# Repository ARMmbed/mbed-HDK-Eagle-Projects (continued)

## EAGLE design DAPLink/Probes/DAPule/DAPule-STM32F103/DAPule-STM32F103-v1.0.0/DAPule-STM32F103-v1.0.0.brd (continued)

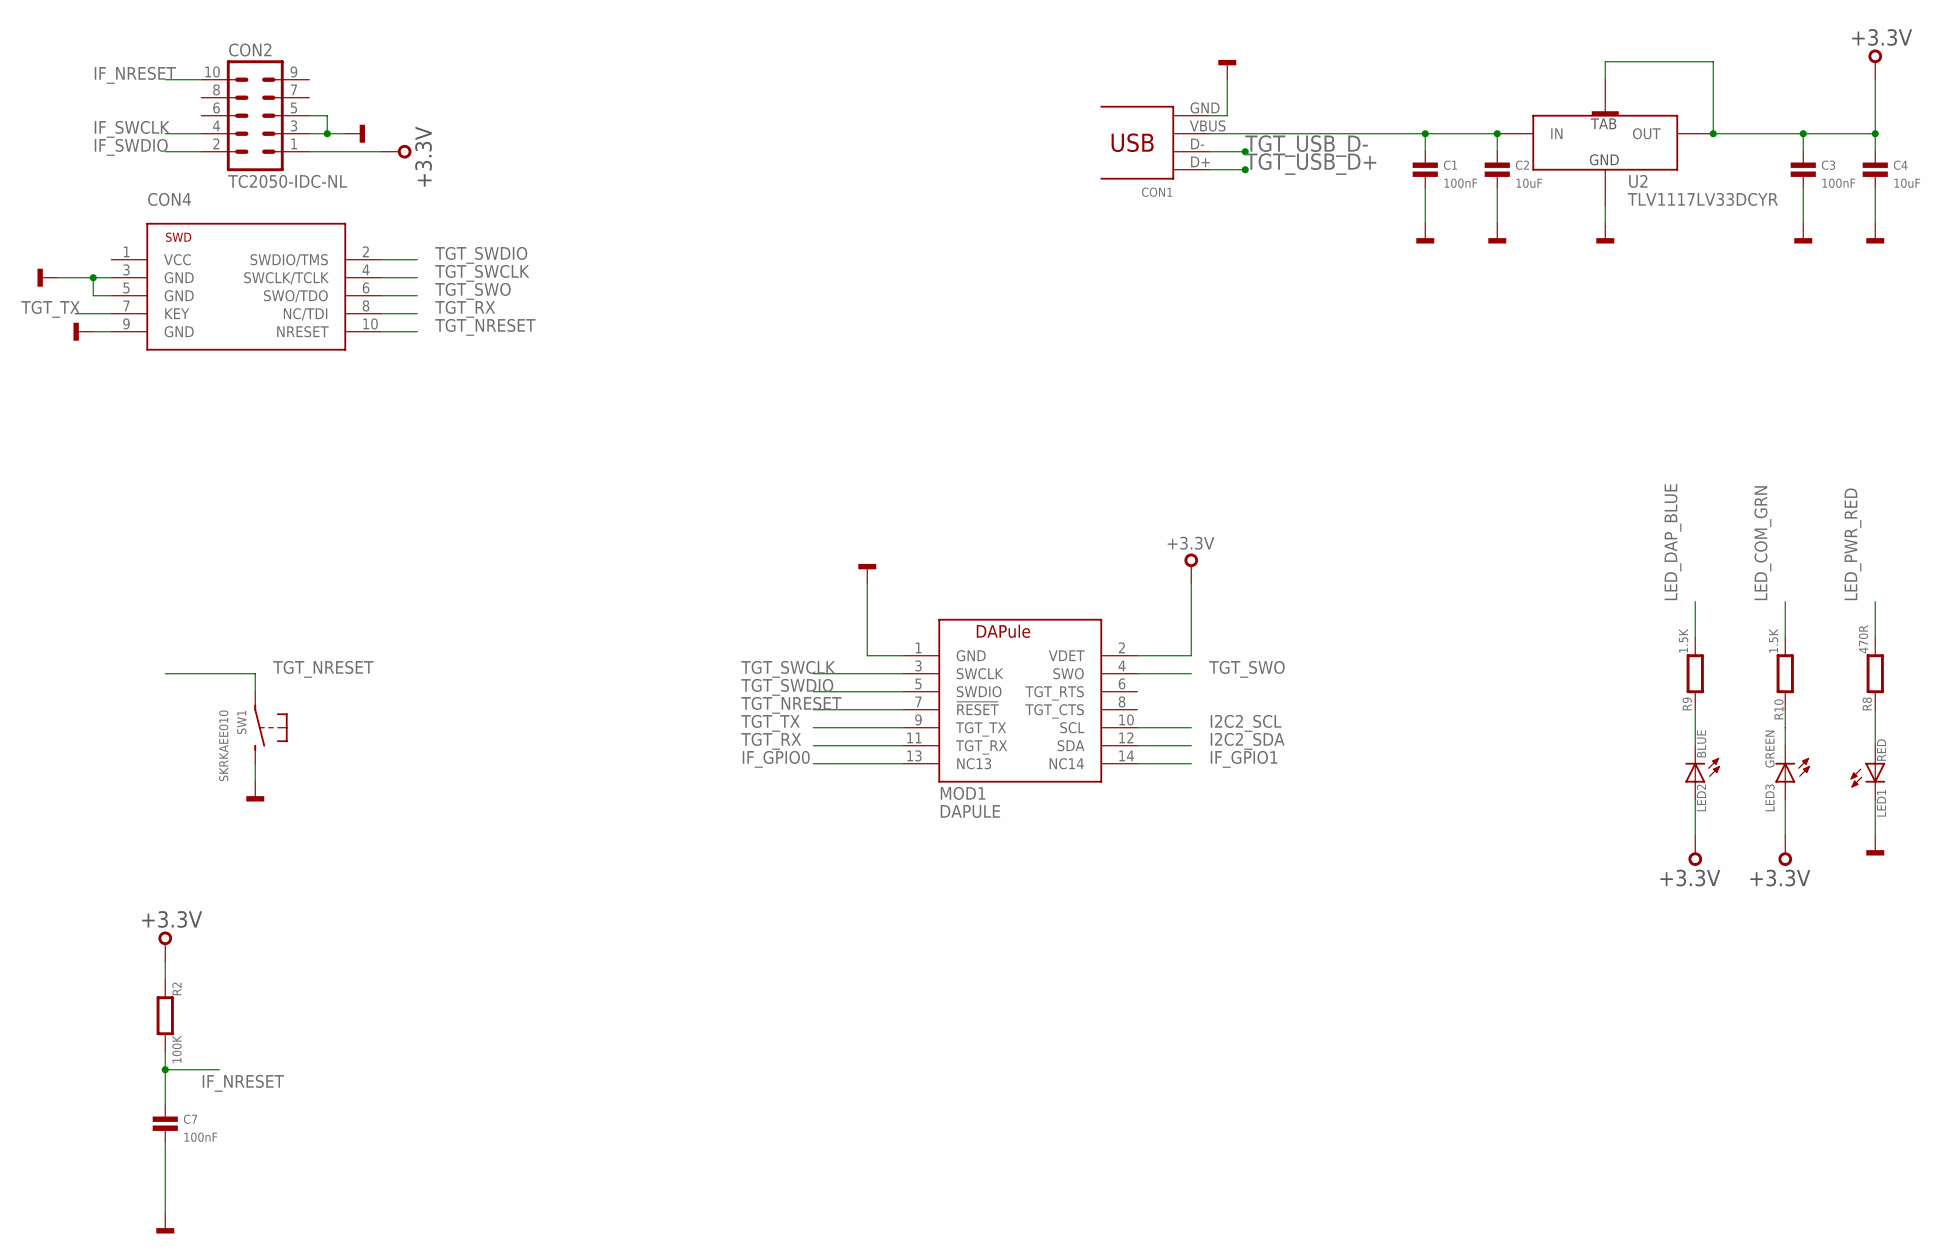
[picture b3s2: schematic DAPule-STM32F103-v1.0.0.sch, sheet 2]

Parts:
C1, C3, C7: 100nF; 0603
C2, C4: 10uF; 0603
CON1: 47346-0001; USB-MICRO-B-H
CON2: TC2050-IDC-NL
CON4: SWD-10-SMD
LED1: RED; CHIPLED_0603
LED2: BLUE; CHIPLED_0603
LED3: GREEN; CHIPLED_0603
MOD1: DAPULE
R2: 100K; 0603
R8: 470R; 0603
R9, R10: 1.5K; 0603
SW1: SKRKAEE010
U2: TLV1117LV33DCYR; SOT223

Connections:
+3.3V: C3.1, C4.1, CON2.1, LED2.A, LED3.A, MOD1.2 (VDET), R2.1, U2.OUT(1) (OUT), U2.OUT(2) (TAB); also elsewhere on the board
GND: C1.2, C2.2, C3.2, C4.2, C7.2, CON1.GND, CON2.3, CON2.5, CON4.3 (GND), CON4.5 (GND), CON4.9 (GND), LED1.C, MOD1.1 (GND), SW1.P$2 (S), U2.GND; also elsewhere on the board
I2C2_SCL: MOD1.10 (SCL); also elsewhere on the board
I2C2_SDA: MOD1.12 (SDA); also elsewhere on the board
IF_GPIO0: MOD1.13 (NC13); also elsewhere on the board
IF_GPIO1: MOD1.14 (NC14); also elsewhere on the board
IF_NRESET: C7.1, CON2.10, R2.2; also elsewhere on the board
IF_SWCLK: CON2.4; also elsewhere on the board
IF_SWDIO: CON2.2; also elsewhere on the board
LED_COM_GRN: R10.2; also elsewhere on the board
LED_DAP_BLUE: R9.2; also elsewhere on the board
LED_PWR_RED: R8.2; also elsewhere on the board
unnamed: C1.1, C2.1, CON1.VBUS, U2.IN
unnamed: LED1.A, R8.1
unnamed: LED2.C, R9.1
unnamed: LED3.C, R10.1
TGT_NRESET: CON4.10 (NRESET), MOD1.7 (!RESET), SW1.P$1; also elsewhere on the board
TGT_RX: CON4.8 (NC/TDI), MOD1.11 (TGT_RX); also elsewhere on the board
TGT_SWCLK: CON4.4 (SWCLK/TCLK), MOD1.3 (SWCLK); also elsewhere on the board
TGT_SWDIO: CON4.2 (SWDIO/TMS), MOD1.5 (SWDIO); also elsewhere on the board
TGT_SWO: CON4.6 (SWO/TDO), MOD1.4 (SWO); also elsewhere on the board
TGT_TX: CON4.7 (KEY), MOD1.9 (TGT_TX); also elsewhere on the board
TGT_USB_D+: CON1.D+; also elsewhere on the board
TGT_USB_D-: CON1.D-; also elsewhere on the board

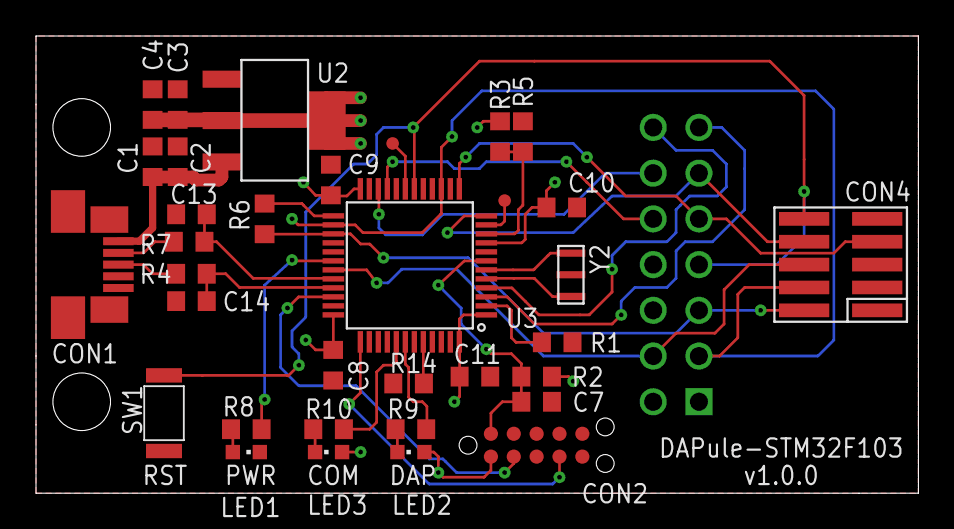
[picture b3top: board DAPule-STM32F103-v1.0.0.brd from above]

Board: 2 copper layers, 49.0 x 25.4 mm, 35 parts (0 on the bottom side), 34 nets.

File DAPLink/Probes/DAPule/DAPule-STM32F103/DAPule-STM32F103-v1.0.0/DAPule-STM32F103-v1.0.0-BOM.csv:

"Qty";"Value";"Device";"Package";"Parts";"Description";"MF";"MFN";"OC-DIGIKEY";"OC-MOUSER";"OC-NEWARK";"TP_SIGNAL_NAME";
"2";"1.5K";"RESISTOR0603";"0603";"R9, R10";"Resistor";"";"";"";"";"";"";
"2";"100K";"RESISTOR0603";"0603";"R2, R14";"Resistor";"";"";"";"";"";"";
"1";"100R";"RESISTOR0603";"0603";"R6";"Resistor";"";"";"";"";"";"";
"7";"100nF";"CAPACITOR0603";"0603";"C1, C3, C7, C8, C9, C10, C11";"Capacitor";"";"";"";"";"";"";
"1";"10K";"RESISTOR0603";"0603";"R1";"Resistor";"";"";"";"";"";"";
"2";"10uF";"CAPACITOR0603";"0603";"C2, C4";"Capacitor";"";"";"";"";"";"";
"2";"18pF";"CAPACITOR0603";"0603";"C13, C14";"Capacitor";"";"";"";"";"";"";
"2";"33R";"RESISTOR0603";"0603";"R4, R7";"Resistor";"";"";"";"";"";"";
"2";"4.7K";"RESISTOR0603";"0603";"R3, R5";"Resistor";"";"";"";"";"";"";
"1";"470R";"RESISTOR0603";"0603";"R8";"Resistor";"";"";"";"";"";"";
"1";"47346-0001";"47346-0001";"USB-MICRO-B-H";"CON1";"USB Receptacle Horizontal Micro Type B";"MOLEX";"47346-0001";"";"538-47346-0001";"1568026";"";
"1";"BLUE";"SMD_LED0603";"CHIPLED_0603";"LED2";"LED SMD, Colour Red";"Wurth Electronics Inc";"150060RS75000";"732-4978-1-ND";"710-150060RS75000";"2322071";"";
"1";"CSTCE8M00G55-R0";"CSTCE8M00G55-R0";"CSTCE8M00G55-R0";"Y2";"Resonator Cermanic, Murata 8MHz 33pF";"Murata";"CSTCE8M00G55-R0";"490-1195-1-ND";"81-CSTCE8M00G55-R0";"2443270";"";
"1";"DAPULE";"DAPULE";"DAPULE";"MOD1";"";"";"";"";"";"";"";
"1";"GREEN";"SMD_LED0603";"CHIPLED_0603";"LED3";"LED SMD, Colour Red";"Wurth Electronics Inc";"150060RS75000";"732-4978-1-ND";"710-150060RS75000";"2322071";"";
"2";"PTR1TP07R";"PTR1TP07R";"TP07R";"TP1, TP2";"TEST PIN";"";"";"";"";"";"";
"1";"RED";"SMD_LED0603";"CHIPLED_0603";"LED1";"LED SMD, Colour Red";"Wurth Electronics Inc";"150060RS75000";"732-4978-1-ND";"710-150060RS75000";"2322071";"";
"1";"SKRKAEE010";"SKRKAEE010";"SKRKAEE010";"SW1";"MOMENTARY SWITCH PUSH VERTICAL (SPST)";"ALPS";"SKRKAEE010";"";"688-SKRKAE";"";"";
"1";"STM32F103CBT6";"STM32F103CBT6";"LQFP48";"U3";"ARM® Cortex®-M3 STM32 F1 Microcontroller IC 32-Bit 72MHz 128KB (128K x 8) FLASH";"STMicroelectronics";"STM32F103CBT6";"497-6288-ND";"511-STM32F103CBT6";"11N8296";"";
"1";"SWD-10-SMD";"SWD-10-SMD";"SWD-10-SMD";"CON4";"2.54mm pitch 10-Pin Cortex Programming Header";"";"";"";"";"";"";
"1";"TC2050-IDC-NL";"TC2050-IDC-NL";"TC2050-IDC-NL";"CON2";"Tag-Connect In Circuit Programming & Debug Cable 10 Pin";"";"";"";"";"";"";
"1";"TLV1117LV33DCYR";"TLV1117LV33DCYR";"SOT223";"U2";"LDO Fixed Regulator 3.3v, 1A";"Texas Instruments";"TLV1117LV33DCYR";"296-28778-1-ND";"595-TLV1117LV33DCYR";"2323647";"";

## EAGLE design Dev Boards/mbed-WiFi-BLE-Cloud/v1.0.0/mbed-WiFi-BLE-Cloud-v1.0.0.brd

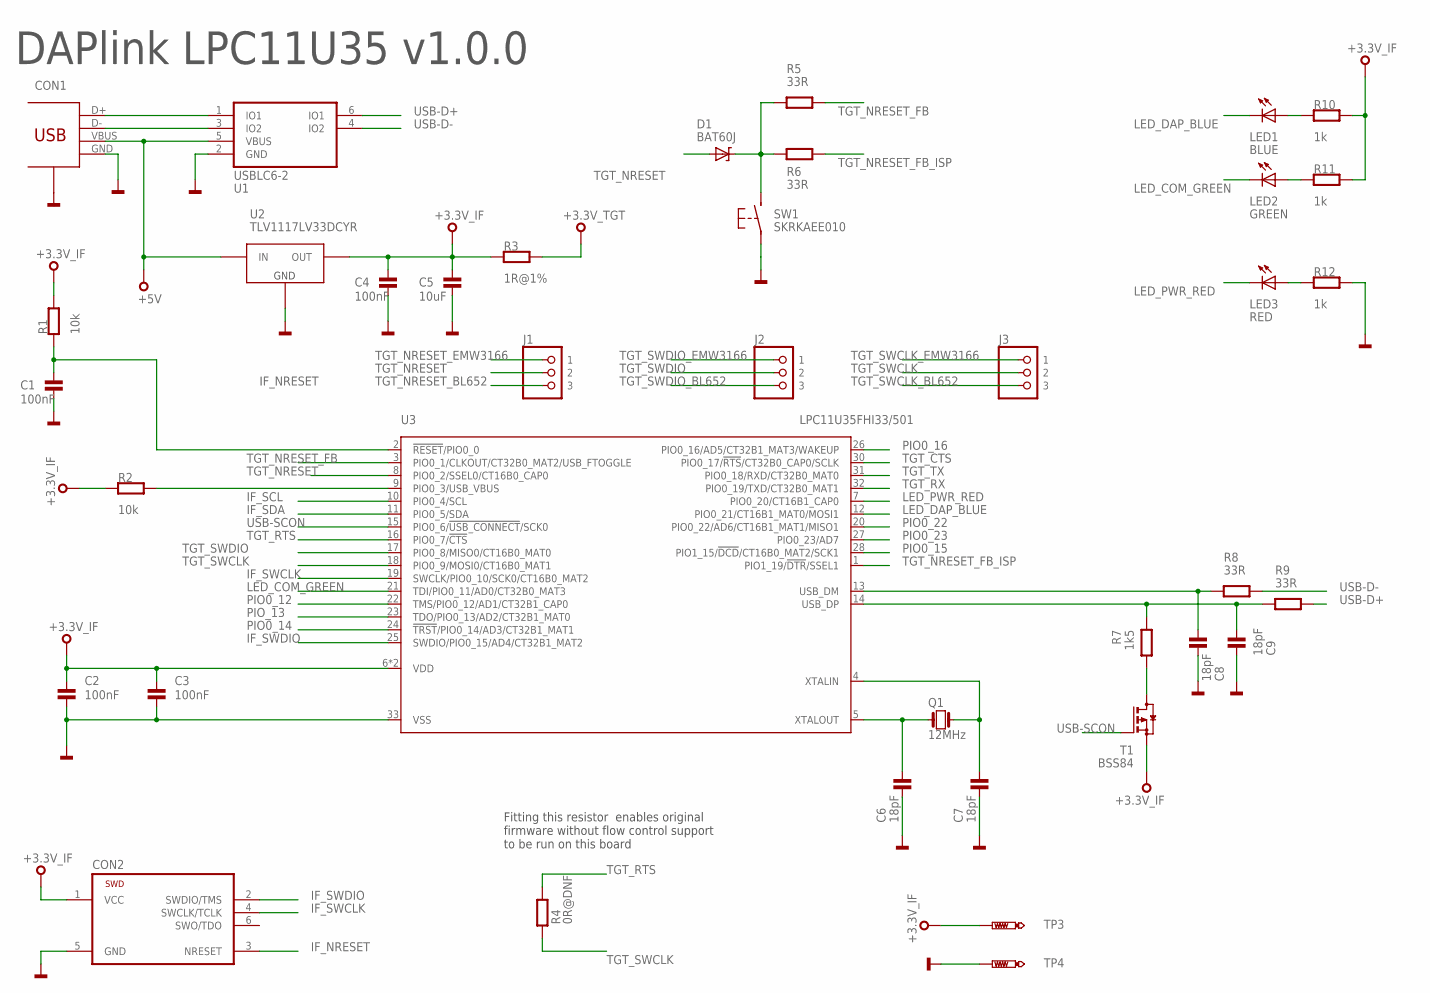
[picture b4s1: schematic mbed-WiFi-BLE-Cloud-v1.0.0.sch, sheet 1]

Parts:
C1, C2, C3, C4: 100nF; 0603
C5: 10uF; 0603
C6, C7, C8, C9: 18pF; 0603
CON1: 47346-0001; USB-MICRO-B-H
CON2: TC2030-CTX-NL
D1: BAT60J; SOD323
J1, J2, J3: PINHD-1X3; 1X03
LED1: BLUE; CHIPLED_0603
LED2: GREEN; CHIPLED_0603
LED3: RED; CHIPLED_0603
Q1: 12MHz; 3.2X.2.5
R1, R2: 10k; 0603
R3: 1R@1%; 0603
R4: 0R@DNF; 0603
R5, R6, R8, R9: 33R; 0603
R7: 1k5; 0603
R10, R11, R12: 1k; 0603
SW1: SKRKAEE010
T1: BSS84; SOT23-3
TP3, TP4: PTR1PAD1-13; P1-13
U1: USBLC6-2SC6; SOT23-6L
U2: TLV1117LV33DCYR; SOT223
U3: LPC11U35FHI33/501; SOT617-3

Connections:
+3.3V_IF: C2.1, C3.1, C4.1, C5.1, CON2.1 (VCC), R1.2, R2.1, R3.1, R10.2, R11.2, T1.2 (S), TP3.TP, U2.2 (OUT), U2.4 (OUT), U3.6 (VDD), U3.29 (VDD); also elsewhere on the board
+3.3V_TGT: R3.2; also elsewhere on the board
+5V: CON1.VBUS, U1.5 (VBUS), U2.3 (IN); also elsewhere on the board
GND: C1.2, C2.2, C3.2, C4.2, C5.2, C6.2, C7.2, C8.2, C9.2, CON1.GND, CON1.GND1 (SHEILD), CON1.GND2 (SHEILD), CON1.GND3 (SHEILD), CON1.GND4 (SHEILD), CON2.5 (GND), R12.2, SW1.P$1, TP4.TP, U1.2 (GND), U2.1 (GND), U3.33 (VSS); also elsewhere on the board
IF_NRESET: C1.1, CON2.3 (NRESET), R1.1, U3.2 (!RESET!/PIO0_0)
IF_SCL: U3.10 (PIO0_4/SCL); also elsewhere on the board
IF_SDA: U3.11 (PIO0_5/SDA); also elsewhere on the board
IF_SWCLK: CON2.4 (SWCLK/TCLK), U3.19 (SWCLK/PIO0_10/SCK0/CT16B0_MAT2)
IF_SWDIO: CON2.2 (SWDIO/TMS), U3.25 (SWDIO/PIO0_15/AD4/CT32B1_MAT2)
LED_COM_GREEN: LED2.C, U3.21 (TDI/PIO0_11/AD0/CT32B0_MAT3)
LED_DAP_BLUE: LED1.C, U3.12 (PIO0_21/CT16B1_MAT0/MOSI1)
LED_PWR_RED: LED3.C, U3.7 (PIO0_20/CT16B1_CAP0)
unnamed: C7.1, Q1.P$3 (2), U3.4 (XTALIN)
unnamed: R7.1, T1.3 (D)
unnamed: C6.1, Q1.P$1 (1), U3.5 (XTALOUT)
unnamed: R2.2, U3.9 (PIO0_3/USB_VBUS)
unnamed: LED2.A, R11.1
unnamed: LED1.A, R10.1
unnamed: LED3.A, R12.1
unnamed: CON1.D-, U1.3 (IO2)
unnamed: CON1.D+, U1.1 (IO1)
PIO0_12: U3.22 (TMS/PIO0_12/AD1/CT32B1_CAP0)
PIO0_14: U3.24 (!TRST!/PIO0_14/AD3/CT32B1_MAT1)
PIO0_15: U3.28 (PIO1_15/!DCD!/CT16B0_MAT2/SCK1)
PIO0_16: U3.26 (PIO0_16/AD5/CT32B1_MAT3/WAKEUP)
PIO0_22: U3.20 (PIO0_22/AD6/CT16B1_MAT1/MISO1)
PIO0_23: U3.27 (PIO0_23/AD7)
PIO_13: U3.23 (TDO/PIO0_13/AD2/CT32B1_MAT0)
TGT_CTS: U3.30 (PIO0_17/!RTS!/CT32B0_CAP0/SCLK)
TGT_NRESET: D1.A, J1.2, U3.8 (PIO0_2/SSEL0/CT16B0_CAP0)
TGT_NRESET_BL652: J1.3; also elsewhere on the board
TGT_NRESET_BUTTON: D1.K, R5.2, R6.2, SW1.P$2 (S)
TGT_NRESET_EMW3166: J1.1; also elsewhere on the board
TGT_NRESET_FB: R5.1, U3.3 (PIO0_1/CLKOUT/CT32B0_MAT2/USB_FTOGGLE)
TGT_NRESET_FB_ISP: R6.1, U3.1 (PIO1_19/!DTR!/SSEL1)
TGT_RTS: R4.2, U3.16 (PIO0_7/!CTS!)
TGT_RX: U3.32 (PIO0_19/TXD/CT32B0_MAT1); also elsewhere on the board
TGT_SWCLK: J3.2, R4.1, U3.18 (PIO0_9/MOSI0/CT16B0_MAT1)
TGT_SWCLK_BL652: J3.3; also elsewhere on the board
TGT_SWCLK_EMW3166: J3.1; also elsewhere on the board
TGT_SWDIO: J2.2, U3.17 (PIO0_8/MISO0/CT16B0_MAT0)
TGT_SWDIO_BL652: J2.3; also elsewhere on the board
TGT_SWDIO_EMW3166: J2.1; also elsewhere on the board
TGT_TX: U3.31 (PIO0_18/RXD/CT32B0_MAT0); also elsewhere on the board
USB-D+: R9.1, U1.6 (IO1)
USB-D-: R8.1, U1.4 (IO2)
USB-SCON: T1.1 (G), U3.15 (PIO0_6/!USB_CONNECT!/SCK0)
USB_DM: C8.1, R8.2, U3.13 (USB_DM)
USB_DP: C9.1, R7.2, R9.2, U3.14 (USB_DP)

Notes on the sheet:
Fitting this resistor enables original firmware without flow control support to be run on this board
DAPlink LPC11U35 v1.0.0

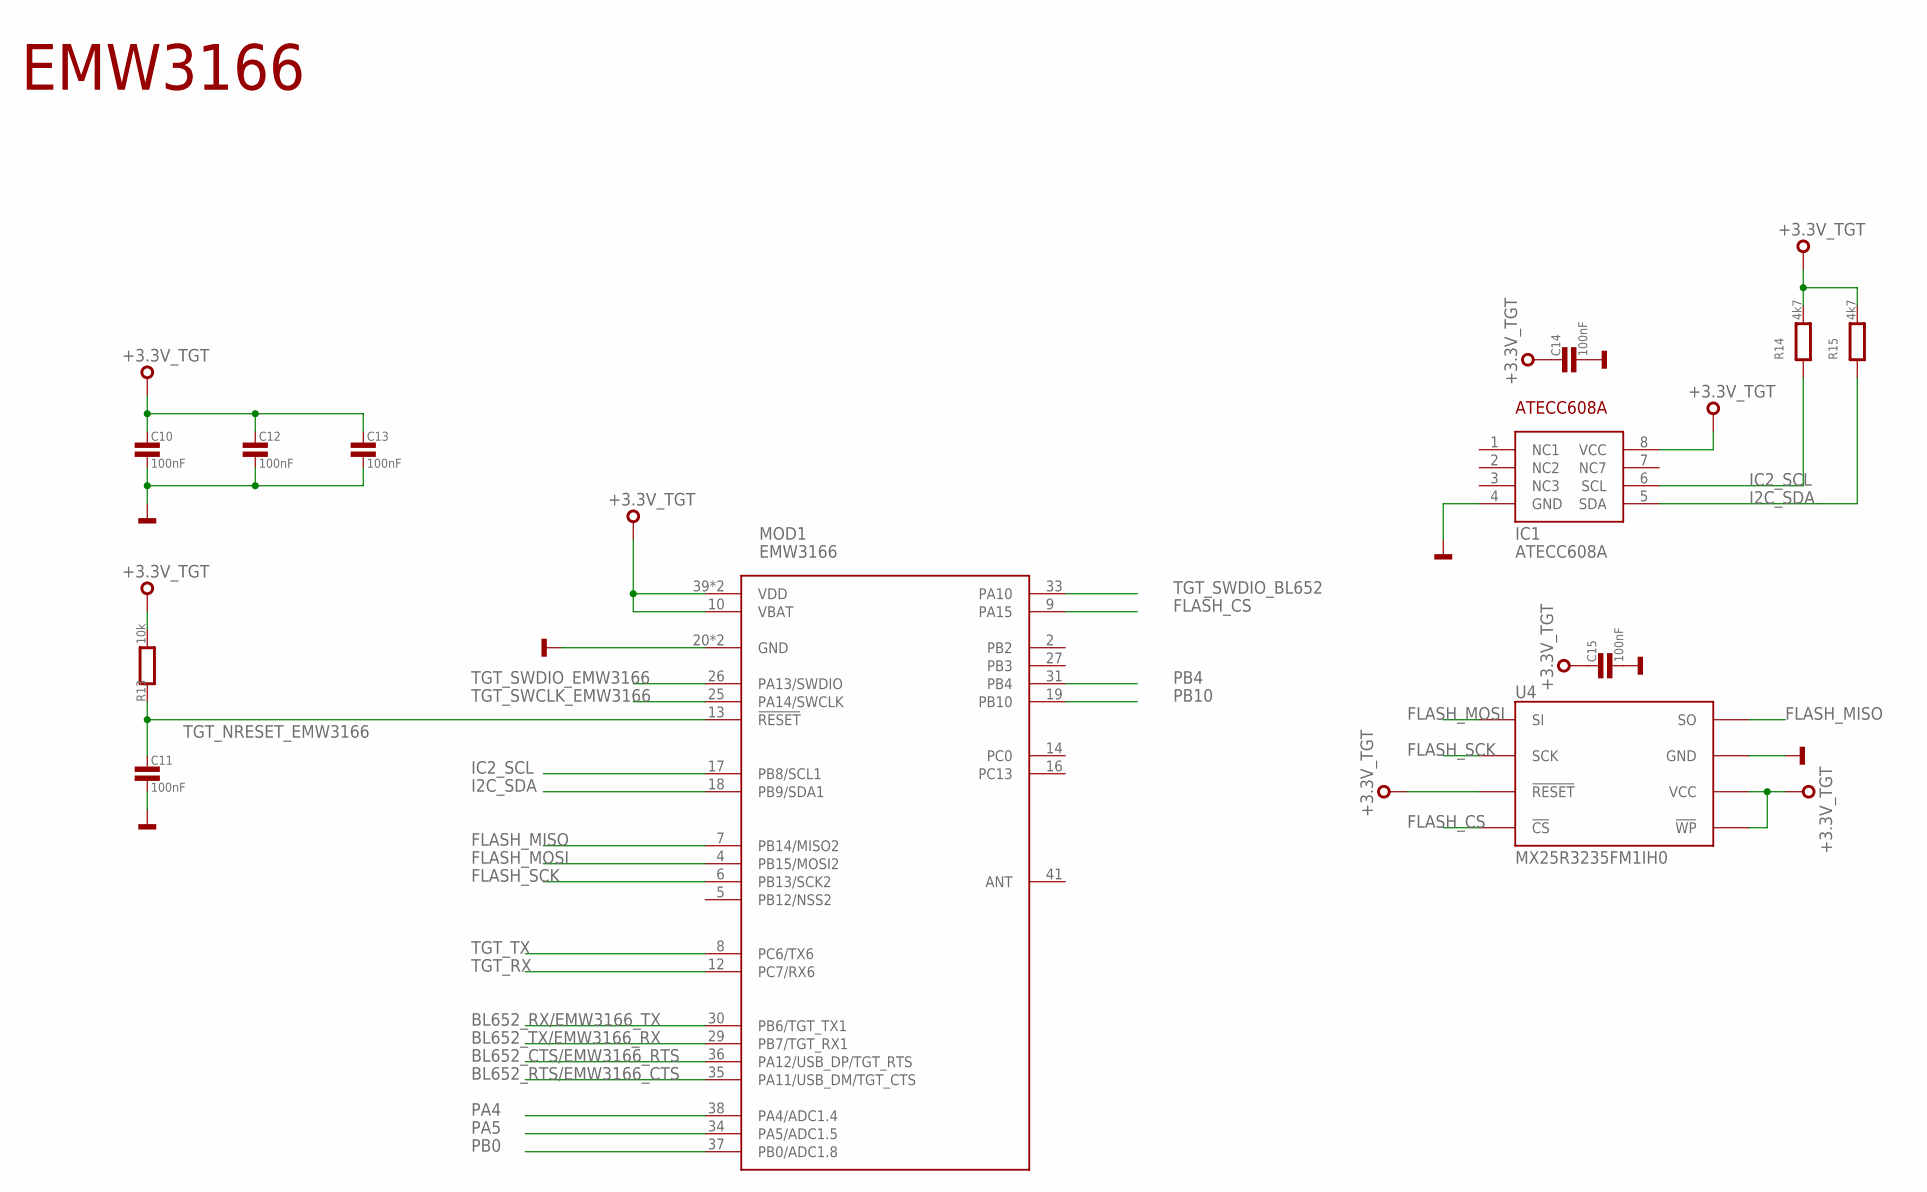
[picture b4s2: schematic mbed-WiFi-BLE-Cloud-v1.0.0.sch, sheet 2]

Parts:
C10, C11, C12, C13, C14, C15: 100nF; 0603
IC1: ATECC608A; SO8
MOD1: EMW3166
R13: 10k; 0603
R14, R15: 4k7; 0603
U4: MX25R3235FM1IH0; SO8

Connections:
+3.3V_TGT: C10.1, C12.1, C13.1, C14.1, C15.1, IC1.8 (VCC), MOD1.10 (VBAT), MOD1.39 (VDD), MOD1.40 (VDD), R13.2, R14.2, R15.2, U4.3 (!WP), U4.7 (!RESET), U4.8 (VCC); also elsewhere on the board
BL652_CTS/EMW3166_RTS: MOD1.36 (PA12/USB_DP/TGT_RTS); also elsewhere on the board
BL652_RTS/EMW3166_CTS: MOD1.35 (PA11/USB_DM/TGT_CTS); also elsewhere on the board
BL652_RX/EMW3166_TX: MOD1.30 (PB6/TGT_TX1); also elsewhere on the board
BL652_TX/EMW3166_RX: MOD1.29 (PB7/TGT_RX1); also elsewhere on the board
FLASH_CS: MOD1.9 (PA15), U4.1 (!CS)
FLASH_MISO: MOD1.7 (PB14/MISO2), U4.2 (SO)
FLASH_MOSI: MOD1.4 (PB15/MOSI2), U4.5 (SI)
FLASH_SCK: MOD1.6 (PB13/SCK2), U4.6 (SCK)
GND: C10.2, C11.2, C12.2, C13.2, C14.2, C15.2, IC1.4 (GND), MOD1.20 (GND), MOD1.21 (GND), U4.4 (GND); also elsewhere on the board
I2C_SDA: IC1.5 (SDA), MOD1.18 (PB9/SDA1), R15.1; also elsewhere on the board
IC2_SCL: IC1.6 (SCL), MOD1.17 (PB8/SCL1), R14.1; also elsewhere on the board
PA4: MOD1.38 (PA4/ADC1.4); also elsewhere on the board
PA5: MOD1.34 (PA5/ADC1.5); also elsewhere on the board
PB0: MOD1.37 (PB0/ADC1.8); also elsewhere on the board
PB4: MOD1.31 (PB4); also elsewhere on the board
PB10: MOD1.19 (PB10); also elsewhere on the board
TGT_NRESET_EMW3166: C11.1, MOD1.13 (!RESET), R13.1; also elsewhere on the board
TGT_RX: MOD1.12 (PC7/RX6); also elsewhere on the board
TGT_SWCLK_EMW3166: MOD1.25 (PA14/SWCLK); also elsewhere on the board
TGT_SWDIO_BL652: MOD1.33 (PA10); also elsewhere on the board
TGT_SWDIO_EMW3166: MOD1.26 (PA13/SWDIO); also elsewhere on the board
TGT_TX: MOD1.8 (PC6/TX6); also elsewhere on the board

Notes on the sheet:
EMW3166

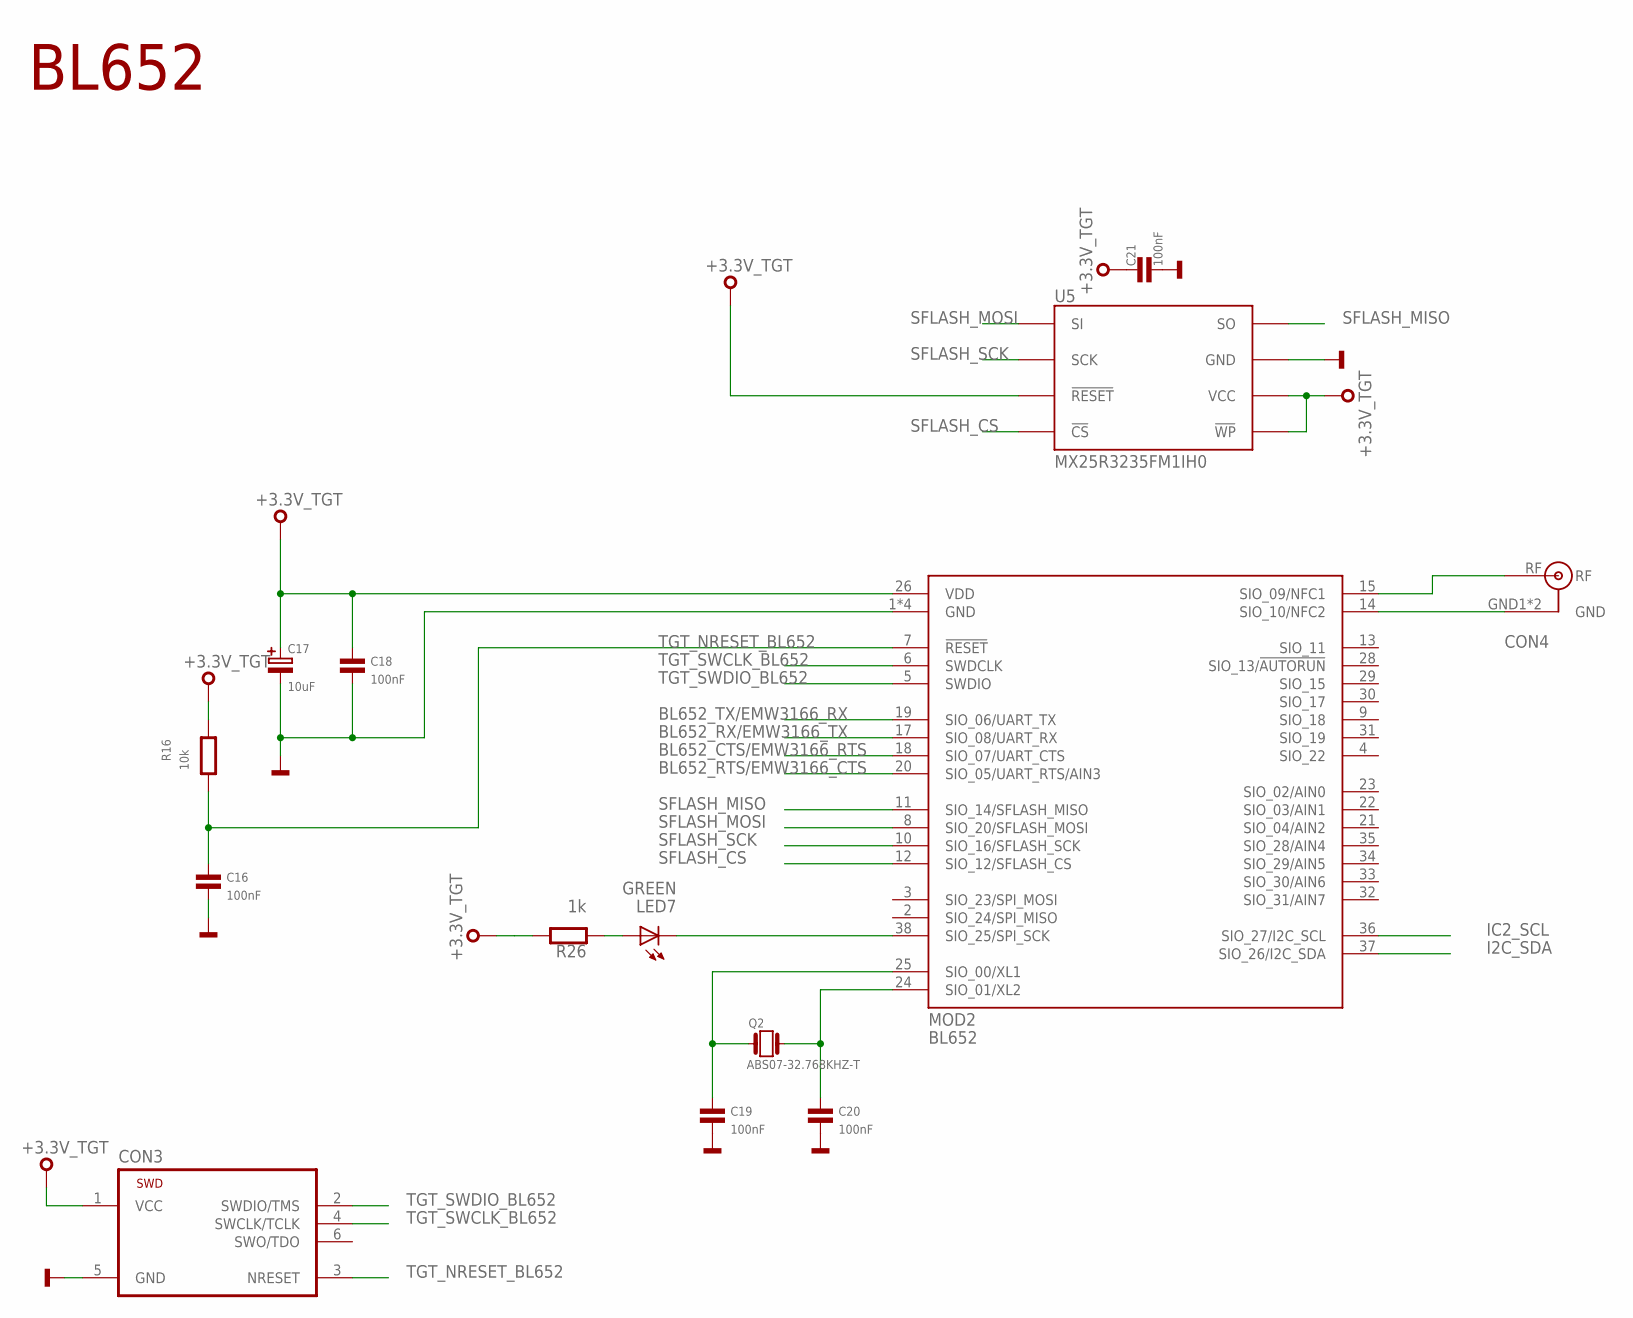
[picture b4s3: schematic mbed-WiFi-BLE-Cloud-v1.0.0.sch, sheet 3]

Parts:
C16, C18, C19, C20, C21: 100nF; 0603
C17: 10uF; SMC_B
CON3: TC2030-CTX-NL
CON4: U.FL; U.FL-R-SMT-1
LED7: GREEN; CHIPLED_0603
MOD2: BL652
Q2: ABS07-32.768KHZ-T; FC135
R16: 10k; 0603
R26: 1k; 0603
U5: MX25R3235FM1IH0; SO8

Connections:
+3.3V_TGT: C17.+, C18.1, C21.1, CON3.1 (VCC), MOD2.26 (VDD), R16.2, R26.2, U5.3 (!WP), U5.7 (!RESET), U5.8 (VCC); also elsewhere on the board
BL652_CTS/EMW3166_RTS: MOD2.18 (SIO_07/UART_CTS); also elsewhere on the board
BL652_RTS/EMW3166_CTS: MOD2.20 (SIO_05/UART_RTS/AIN3); also elsewhere on the board
BL652_RX/EMW3166_TX: MOD2.17 (SIO_08/UART_RX); also elsewhere on the board
BL652_TX/EMW3166_RX: MOD2.19 (SIO_06/UART_TX); also elsewhere on the board
GND: C16.2, C17.-, C18.2, C19.2, C20.2, C21.2, CON3.5 (GND), MOD2.1 (GND), MOD2.16 (GND), MOD2.27 (GND), MOD2.39 (GND), U5.4 (GND); also elsewhere on the board
I2C_SDA: MOD2.37 (SIO_26/I2C_SDA); also elsewhere on the board
IC2_SCL: MOD2.36 (SIO_27/I2C_SCL); also elsewhere on the board
unnamed: CON4.RF, MOD2.15 (SIO_09/NFC1)
unnamed: CON4.GND1 (GND), CON4.GND2 (GND), MOD2.14 (SIO_10/NFC2)
unnamed: LED7.A, R26.1
unnamed: LED7.C, MOD2.38 (SIO_25/SPI_SCK)
unnamed: C20.1, MOD2.24 (SIO_01/XL2), Q2.X2 (2)
unnamed: C19.1, MOD2.25 (SIO_00/XL1), Q2.X1 (1)
SFLASH_CS: MOD2.12 (SIO_12/SFLASH_CS), U5.1 (!CS)
SFLASH_MISO: MOD2.11 (SIO_14/SFLASH_MISO), U5.2 (SO)
SFLASH_MOSI: MOD2.8 (SIO_20/SFLASH_MOSI), U5.5 (SI)
SFLASH_SCK: MOD2.10 (SIO_16/SFLASH_SCK), U5.6 (SCK)
TGT_NRESET_BL652: C16.1, CON3.3 (NRESET), MOD2.7 (!RESET), R16.1; also elsewhere on the board
TGT_SWCLK_BL652: CON3.4 (SWCLK/TCLK), MOD2.6 (SWDCLK); also elsewhere on the board
TGT_SWDIO_BL652: CON3.2 (SWDIO/TMS), MOD2.5 (SWDIO); also elsewhere on the board

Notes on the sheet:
BL652

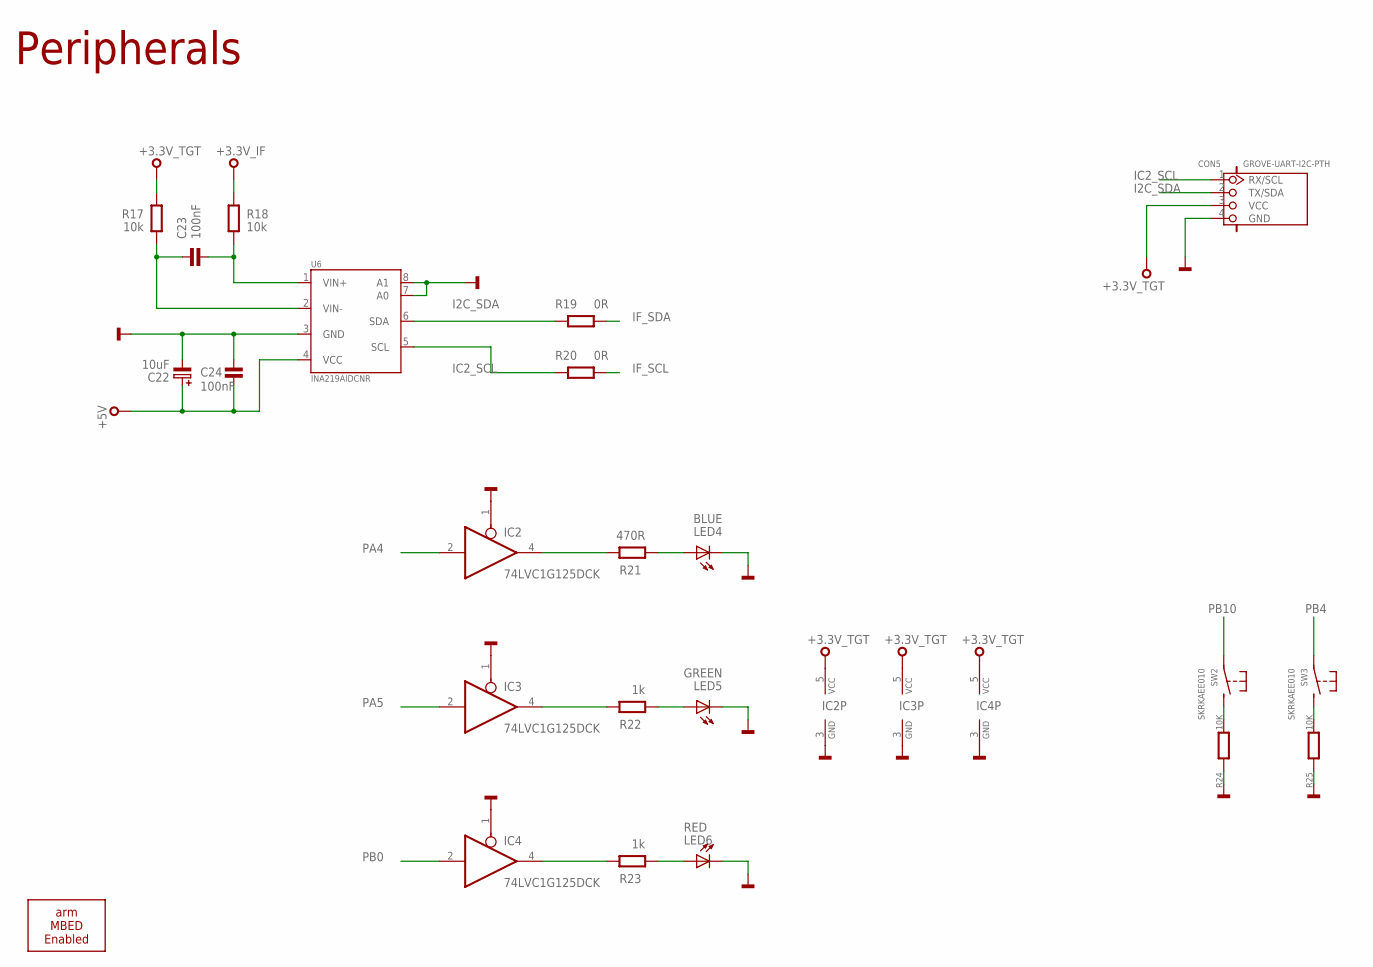
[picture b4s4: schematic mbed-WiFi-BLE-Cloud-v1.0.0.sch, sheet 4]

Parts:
C22: 10uF; CASE-B
C23, C24: 100nF; 0603
CON5: GROVE-UART-I2C-PTH; HW4-2.0
IC2, IC3, IC4: 74LVC1G125DCK; SC70-5
LED4: BLUE; CHIPLED_0603
LED5: GREEN; CHIPLED_0603
LED6: RED; CHIPLED_0603
R17, R18: 10k; 0603@1
R19, R20: 0R; 0603@1
R21: 470R; 0603@1
R22, R23: 1k; 0603@1
R24, R25: 10K; 0603
SS1: ARM-MBED-ENABLED-12MM
SW2, SW3: SKRKAEE010
U6: INA219AIDCNR; SOT23-8

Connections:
+3.3V_IF: R18.2; also elsewhere on the board
+3.3V_TGT: CON5.3 (VCC), IC2.5 (VCC), IC3.5 (VCC), IC4.5 (VCC), R17.2; also elsewhere on the board
+5V: C22.1, C24.2, U6.4 (VCC); also elsewhere on the board
GND: C22.2, C24.1, CON5.4 (GND), IC2.1 (OE), IC2.3 (GND), IC3.1 (OE), IC3.3 (GND), IC4.1 (OE), IC4.3 (GND), LED4.C, LED5.C, LED6.C, R24.1, R25.1, U6.3 (GND), U6.7 (A0), U6.8 (A1); also elsewhere on the board
I2C_SDA: CON5.2 (TX/SDA), R19.2, U6.6 (SDA); also elsewhere on the board
IC2_SCL: CON5.1 (RX/SCL), R20.2, U6.5 (SCL); also elsewhere on the board
IF_SCL: R20.1; also elsewhere on the board
IF_SDA: R19.1; also elsewhere on the board
unnamed: LED5.A, R22.2
unnamed: IC4.4 (O), R23.1
unnamed: LED6.A, R23.2
unnamed: IC3.4 (O), R22.1
unnamed: IC2.4 (O), R21.1
unnamed: LED4.A, R21.2
unnamed: C23.2, R17.1, U6.2 (VIN-)
unnamed: C23.1, R18.1, U6.1 (VIN+)
unnamed: R25.2, SW3.P$2 (S)
unnamed: R24.2, SW2.P$2 (S)
PA4: IC2.2 (I); also elsewhere on the board
PA5: IC3.2 (I); also elsewhere on the board
PB0: IC4.2 (I); also elsewhere on the board
PB4: SW3.P$1; also elsewhere on the board
PB10: SW2.P$1; also elsewhere on the board

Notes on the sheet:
Peripherals

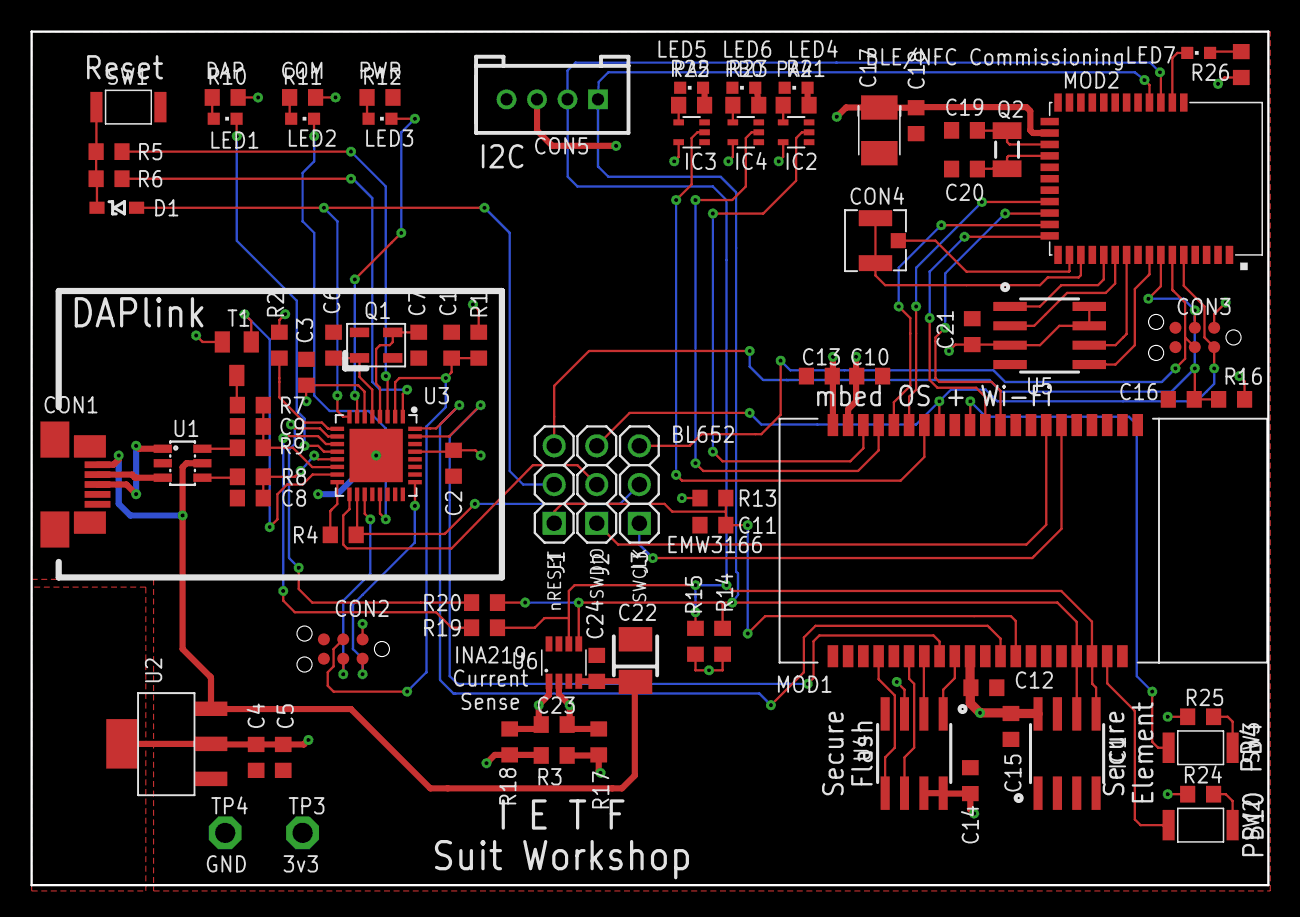
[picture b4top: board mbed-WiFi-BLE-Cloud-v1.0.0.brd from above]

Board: 2 copper layers, 81.2 x 56.0 mm, 87 parts (0 on the bottom side), 76 nets.

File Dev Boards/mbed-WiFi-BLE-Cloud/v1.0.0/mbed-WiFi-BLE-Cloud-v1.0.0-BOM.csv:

"Qty";"Value";"Device";"Package";"Parts";"Description";"MF";"MFN";"OC-DIGIKEY";"OC-MOUSER";"OC-NEWARK";"TP_SIGNAL_NAME";
"3";"";"PINHD-1X3";"1X03";"J1, J2, J3";"PIN HEADER";"";"";"";"";"";"";
"2";"0R";"R0603";"0603@1";"R19, R20";"";"";"";"";"";"";"";
"1";"0R@DNF";"R0603";"0603";"R4";"Resistor";"";"";"";"";"";"";
"10";"100nF";"C0603";"0603";"C1, C2, C3, C4, C16, C18, C19, C20, C23, C24";"Capacitor";"";"";"";"";"";"";
"7";"100nF";"CAPACITOR0603";"0603";"C10, C11, C12, C13, C14, C15, C21";"Capacitor";"";"";"";"";"";"";
"2";"10K";"RESISTOR0603";"0603";"R24, R25";"Resistor";"";"";"";"";"";"";
"4";"10k";"R0603";"0603";"R1, R2, R17, R18";"";"";"";"";"";"";"";
"2";"10k";"RESISTOR0603";"0603";"R13, R16";"Resistor";"";"";"";"";"";"";
"1";"10uF";"C-POL_B";"CASE-B";"C22";"Polarised capacitor";"";"";"";"";"";"";
"1";"10uF";"C0603";"0603";"C5";"Capacitor";"";"";"";"";"";"";
"1";"10uF";"CAPACITOR-POLARISEDB";"SMC_B";"C17";"Polarised capacitor";"Kemet";"T491B106K020AT";"399-8298-1-ND";"80-T491B106K020";" 57K1740";"";
"1";"12MHz";"Q_3.2X2.5";"3.2X.2.5";"Q1";"Generic Crystal";"";"";"";"";"";"";
"4";"18pF";"C0603";"0603";"C6, C7, C8, C9";"Capacitor";"";"";"";"";"";"";
"1";"1R@1%";"R0603";"0603";"R3";"Resistor";"";"";"";"";"";"";
"6";"1k";"R0603";"0603";"R10, R11, R12, R26, R22, R23";"";"";"";"";"";"";"";
"1";"1k5";"R0603";"0603";"R7";"Resistor";"";"";"";"";"";"";
"4";"33R";"R0603";"0603";"R5, R6, R8, R9";"Resistor";"";"";"";"";"";"";
"1";"470R";"R0603";"0603@1";"R21";"";"";"";"";"";"";"";
"1";"47346-0001";"47346-0001";"USB-MICRO-B-H";"CON1";"USB Receptacle Horizontal Micro Type B";"MOLEX";"47346-0001";"WM17141CT-ND";"538-47346-0001";"1568026";"";
"2";"4k7";"RESISTOR0603";"0603";"R14, R15";"Resistor";"";"";"";"";"";"";
"3";"74LVC1G125DCK";"74LVC1G125DCK";"SC70-5";"IC2, IC3, IC4";"Single Bus Buffer Gate with 3-State Output";"";"";"";"";"";"";
"1";"ABS07-32.768KHZ-T";"ABS07-32.768KHZ-T";"FC135";"Q2";"Crystal, Abracon 32.768kHz ±20ppm 12.5pF";"Abracon";"ABS07-32.768KHZ-T";"535-9542-1-ND";"535-9542-1-ND";"2101347";"";
"1";"ARM-MBED-ENABLED-12MM";"ARM-MBED-ENABLED-12MM";"ARM-MBED-ENABLED-12MM";"SS1";"";"";"";"";"";"";"";
"1";"ATECC608A";"ATECC608A";"SO8";"IC1";"";"";"";"";"";"";"";
"1";"BAT60J";"BAT60J";"SOD323";"D1";"SCHOTTKY DIODE";"STMicroelectronics";"BAT60JFILM";"497-3707-6-ND";"511-BAT60JFILM";"89K1218";"";
"1";"BL652";"BL652";"BL652";"MOD2";"";"";"";"";"";"";"";
"2";"BLUE";"LED0603";"CHIPLED_0603";"LED1, LED4";"SMD LED";"";"";"";"";"";"";
"1";"BSS84";"BSS84";"SOT23-3";"T1";"MOSFET P-CHANNEL";"Fairchild Semiconductor";"BSS84";"BSS84CT-ND";"512-BSS84";"58K8770";"";
"1";"EMW3166";"EMW3166";"EMW3166";"MOD1";"";"";"";"";"";"";"";
"3";"GREEN";"LED0603";"CHIPLED_0603";"LED2, LED5, LED7";"LED SMD";"";"";"";"";"";"";
"1";"GROVE-UART-I2C-PTH";"GROVE-UART-I2C-PTH";"HW4-2.0";"CON5";"";"";"";"";"";"";"";
"1";"INA219AIDCNR";"INA219AIDCNR";"SOT23-8";"U6";"Current Sense - I2C";"Texas Instruments";"INA219AIDCNR";"296-23770-1-ND";"595-INA219AIDCNR";"2295989";"";
"1";"LPC11U35FHI33/501";"LPC11U35FHI33/501";"SOT617-3";"U3";"32 Bit Microcontroller, ARM Cortex-M0, 50 MHz, 64 KB, 12 KB, 33 Pins, HVQFN";"NXP";"LPC11U35FHI33/501";"568-9586-ND";"771-LPC11U35FHI33501";"2115658";"";
"2";"MX25R3235FM1IH0";"MX25R3235FM1IH0";"SO8";"U4, U5";"Serial Flash 32 Mb 80 Mhz";"Macronix";"MX25R3235FM2IH0";"1092-1174-ND";"";"";"";
"2";"PTR1PAD1-13";"PTR1PAD1-13";"P1-13";"TP3, TP4";"TEST PIN";"";"";"";"";"";"";
"2";"RED";"LED0603";"CHIPLED_0603";"LED3, LED6";"SMD LED";"";"";"";"";"";"";
"3";"SKRKAEE010";"SKRKAEE010";"SKRKAEE010";"SW1, SW2, SW3";"MOMENTARY SWITCH PUSH VERTICAL (SPST)";"ALPS";"SKRKAEE010";"";"688-SKRKAE";"";"";
"2";"TC2030-CTX-NL";"TC2030-CTX-NL";"TC2030-CTX-NL";"CON2, CON3";"Tag-Connect In Circuit Programming & Debug Cable 6 Pin";"";"";"";"";"";"";
"1";"TLV1117LV33DCYR";"TLV1117LV33DCYR";"SOT223";"U2";"LDO Fixed Regulator 3.3v, 1A";"Texas Instruments";"TLV1117LV33DCYR";"296-28778-1-ND";"595-TLV1117LV33DCYR";"2323647";"";
"1";"U.FL";"U.FL";"U.FL-R-SMT-1";"CON4";"";"Hirose";"U.FL-R-SMT-1";"H9161CT-ND";"798-U.FL-R-SMT-110";"1688077";"";
"1";"USBLC6-2SC6";"USBLC6-2SC6";"SOT23-6L";"U1";"";"";"";"";"";"";"";
